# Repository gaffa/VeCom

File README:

VeCom is an open source Vehicle Computer that was also my bachelors thesis

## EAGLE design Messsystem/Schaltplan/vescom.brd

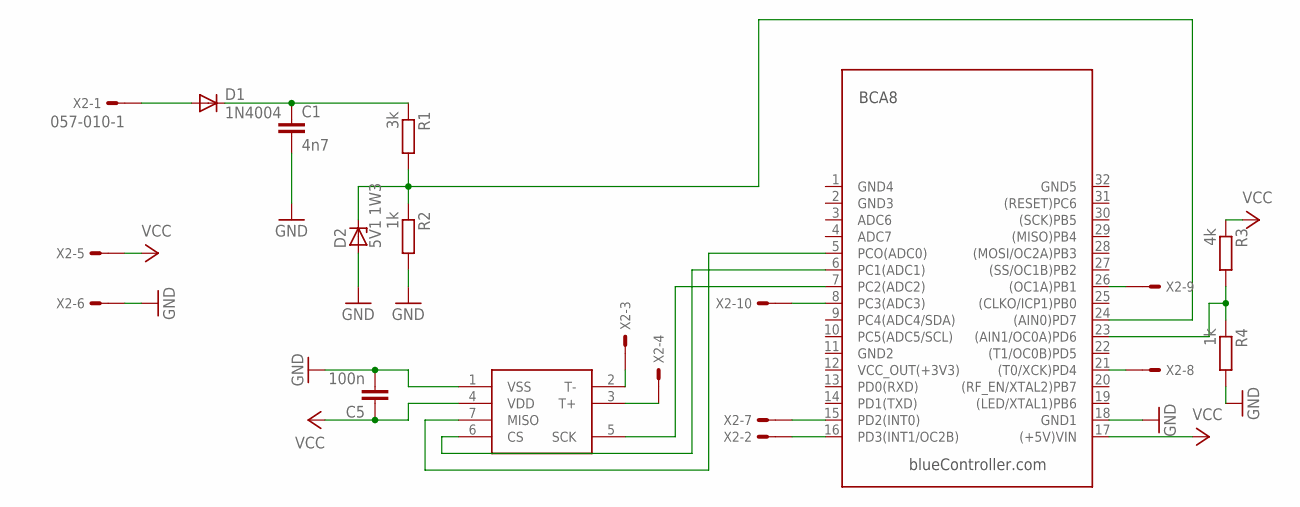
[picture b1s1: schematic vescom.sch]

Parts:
C1: 4n7; C025-025X050
C5: 100n; C025-025X050
D1: 1N4004; DO41-10
D2: 5V1 1W3; DO34Z7
MAX6675: MAX6675; SO08
R1: 3k; 0207/10
R2, R4: 1k; 0207/10
R3: 4k; 0207/10
U$1: BC
X2: 057-010-1

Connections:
EGT_CK: MAX6675.5 (SCK), U$1.7 (PC2(ADC2))
EGT_CS: MAX6675.6 (CS), U$1.6 (PC1(ADC1))
EGT_MISO: MAX6675.7 (MISO), U$1.5 (PCO(ADC0))
GND: C1.2, C5.2, D2.A, MAX6675.1 (VSS), R2.2, R4.2, U$1.18 (GND1), X2.6
LICHTMASCHINE: D1.A, X2.1
unnamed: U$1.21 ((T0/XCK)PD4), X2.8
unnamed: C1.1, D1.C, R1.1
unnamed: U$1.16 (PD3(INT1/OC2B)), X2.2
unnamed: U$1.15 (PD2(INT0)), X2.7
unnamed: R3.2, R4.1, U$1.23 ((AIN1/OC0A)PD6)
unnamed: U$1.26 ((OC1A)PB1), X2.9
PC3: U$1.8 (PC3(ADC3)), X2.10
RPM_Q: D2.C, R1.2, R2.1, U$1.24 ((AIN0)PD7)
T+: MAX6675.3 (T+), X2.4
T-: MAX6675.2 (T-), X2.3
VCC: C5.1, MAX6675.4 (VDD), R3.1, U$1.17 ((+5V)VIN), X2.5

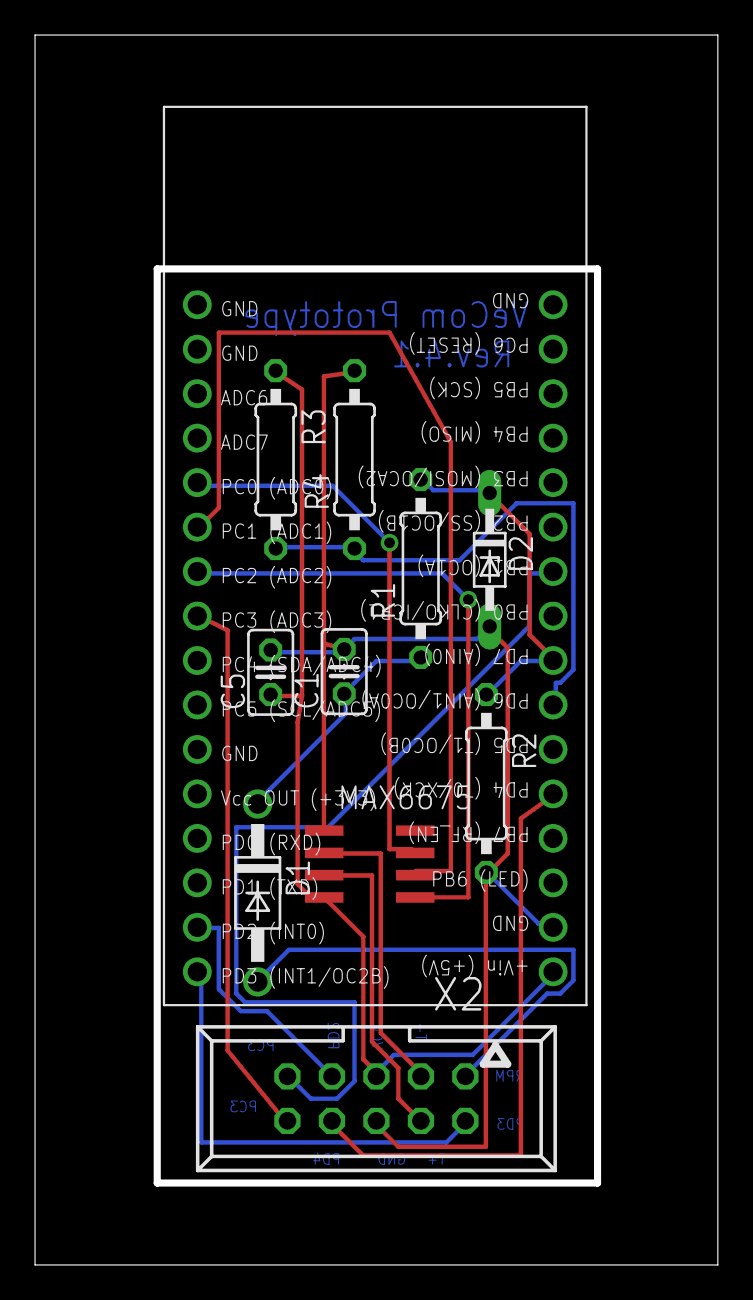
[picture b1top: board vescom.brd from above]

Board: 2 copper layers, 38.6 x 69.8 mm, 11 parts (0 on the bottom side), 16 nets.

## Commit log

2012-11-25 initial import
2012-11-28 eclipseified and some minor changes
2012-11-28 removes .idea folder (committed by mistake)
2012-11-28 removes more unneeded stuff
2012-12-02 fixed bug in egt-routine and migrated project to atmel studio6
2012-12-03 Added ACRA (Application Crash Report for Android) and fixed Eclipse build
2012-12-09 removal of ba
2013-07-23 cleanup
